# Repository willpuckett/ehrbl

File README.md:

# 🍁 ehrbl

> a tiny board to celebrate the coming of 🍂 with minimal finger travel.

After spending the day at my computer, I stepped out with friends Saturday night
for a burger. On the patio of our local institution, the air was
cool.

> _Autumn had undeniably arrived._

I had been wanting to squeeze a Ferris Sweep out of a Xiao somehow and it
occurred to me as I later continued working that maybe I was actually trying to
make a 28 key keyboard. I reached for a leaf to lay over the keys: the maple fit
nicely, conjuring memories of _beurre d'érable_ (maple butter) in Montreal's
Jean-Talon Market.

## BOM

|      QTY      |             Part             | JLCPCB Part # |
| :-----------: | :--------------------------: | :-----------: |
|       2       |         MY-LR44-03-J         |   C5457116    |
|       4       |       100 nF 0402 cap        |    C60474     |
|       2       |          SSSS811101          |    C109335    |
|       4       |      MF254V-11-07-0743       |   C2889988    |
|       6       |          CESD5V0D3           |    C22643     |
|       2       |   0906-2-15-20-75-14-11-0    |   C5261048    |
|       8       |           UMP1NTR            |    C510065    |
| 56 (optional) |   3305-0-15-80-47-27-10-0    |   C17370797   |
|     26/28     |       ChocV1 switches        |      N/A      |
| 2 (optional)  | Panasonic EVQWGD001 encoders |      N/A      |
|       2       |   3.7V LIR1254 (NOT LR44)    |      N/A      |
|       2       |        Xiao nRF52840         |      N/A      |

## Putting it Together

### Fabrication & Assembly Files [[zip](https://github.com/willpuckett/ehrbl/releases/latest/download/jlcpcb.zip)]

JLC likes to install the 3305's upside down. Include
[this pic](.images/3305-installation.png) along with a note requesting they be
installed thru-hole.

Choose 28 keys, or 26 keys with encoders.

> [!CAUTION]
> Use **3.7v LIR1254** (lithium ion rechargable) battery **only**, being sure to
> not install it upside down.

Also available [here](https://octule.com/listing/1842166746/ehrbl).

## Case

### There's a case [[step](https://github.com/willpuckett/ehrbl/releases/latest/download/case.step)] [[stl](https://github.com/willpuckett/ehrbl/releases/latest/download/case.step)]

It's really more of a skin. It is designed to sit as low as possible.Print and place the pcb directly in it. The case is
only one half, flip it in your slicer for the other half 🙃

> [!TIP]
> Polymaker TPU works well. It seems to like to print slow and cool—leave the
> door ajar.

TPU is relatively non-slip, and it absorbs and distributes the force of
typing—no bumpons necessary.

## Caster

### Download the latest firmware [[left](https://github.com/willpuckett/ehrbl/releases/latest/download/ehrbl-central.uf2)] [[right](https://github.com/willpuckett/ehrbl/releases/latest/download/ehrbl-peripheral.uf2)]

Using a variant that should probably be referred to as _Befuddle_, scoring a
whispy 636.1 "total word effort" on
[cyanophage](https://cyanophage.github.io/playground.html?layout=bfdl%2F%3Bpouyjcstrx-naihqvwgm%5C%3Dk%2C.%27ze&mode=ergo&lan=english), this maple is buttery indeed. The Y-punctuation cluster interaction is its greatest shortcoming, but it seems
to be the least of all evils and becomes more natural after a week or so.

Optimized for single handed CAD—Blender, KiCad, Shapr... Hold num/caps word to access the upside down sticky layer which reverses the keys. You'll have all the alphas on both hands and don't have to switch back and forth from mouse/trackpad so much.

> [!NOTE]
> The combo-forward layout obscures CAGS home row mods in the graphics.

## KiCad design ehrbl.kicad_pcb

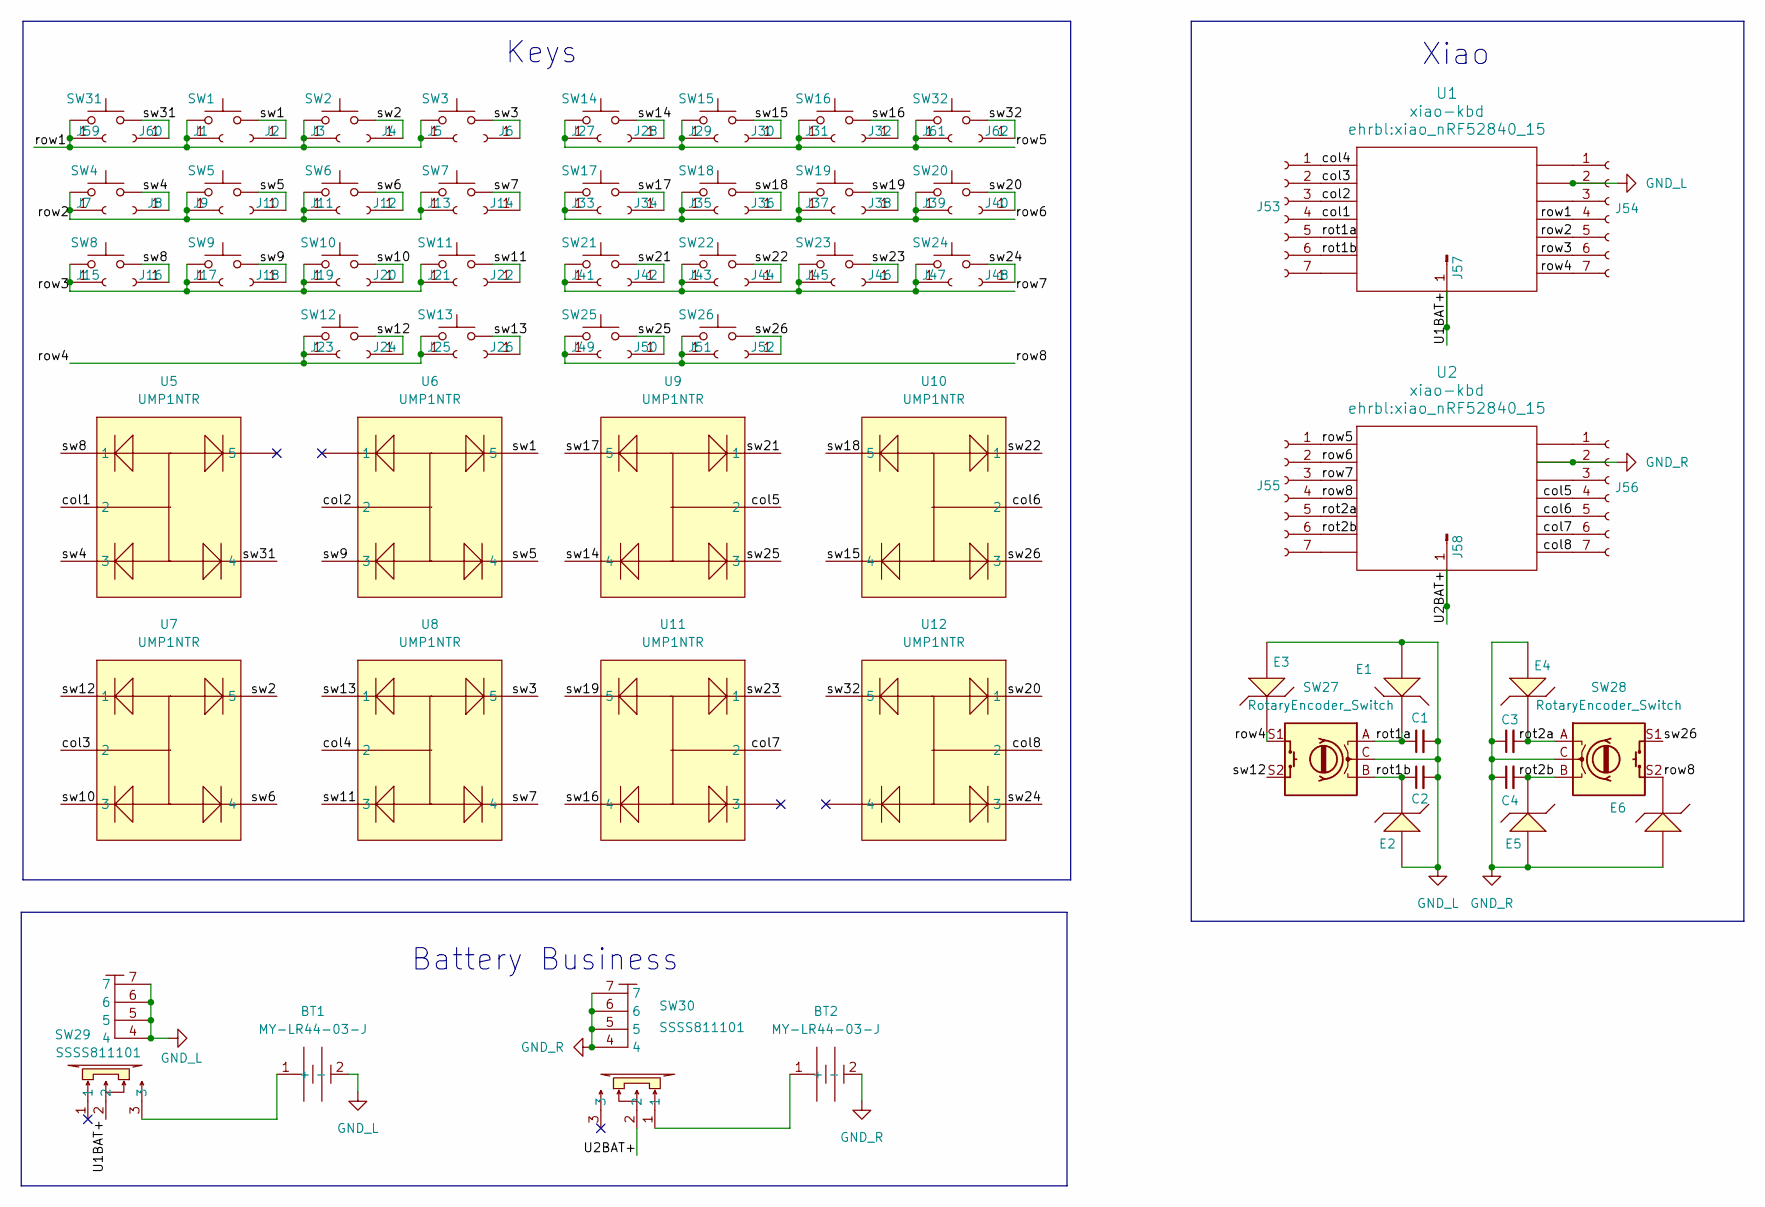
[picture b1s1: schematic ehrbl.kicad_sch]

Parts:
BT1, BT2: MY-LR44-03-J; CONN-TH_MY-LR44-03-J; LCSC C5457116
C1, C2, C3, C4: C_Small; C_0402_1005Metric; LCSC C60474
E1, E2, E3, E4, E5, E6: CESD5V0D3 ZA; SOD-323_L1.8-W1.3-LS2.5-RD; LCSC C22643
J1, J2, J3, J4, J5, J6, J7, J8, J9, J10, J11, J12, J13, J14, J15, J16, J17, J18, J19, J20, J21, J22, J23, J24, J25, J26, J27, J28, J29, J30, J31, J32, J33, J34, J35, J36, J37, J38, J39, J40, J41, J42, J43, J44, J45, J46, J47, J48, J49, J50, J51, J52, J59, J60, J61, J62: 3305-0-15-80-47-27-10-0; MPN 3305-0-15-80-47-27-10-0; LCSC C17370797
J53, J54, J55, J56: MF254V-11-07-0743; MPN 310-13-107-41-001000; LCSC C2889988
J57, J58: 0906; 0906-2-15-20-75-14-11-0; MPN 0906-2-15-20-75-14-11-0; LCSC C5261048
SW1, SW2, SW3, SW4, SW5, SW6, SW7, SW8, SW9, SW10, SW11, SW12, SW13, SW14, SW15, SW16, SW17, SW18, SW19, SW20, SW21, SW22, SW23, SW24, SW25, SW26, SW31, SW32: SW_Push; SW_PG1350
SW27, SW28: RotaryEncoder_Switch; RollerEncoder_Panasonic_EVQWGD001
SW29, SW30: SSSS811101; SW-SMD_SSSS811101; LCSC C109335
U1, U2: xiao-kbd; xiao_nRF52840_15
U5, U7, U8, U9, U10, U11, U12: UMP1NTR; SOT-353_L2.1-W1.3-P0.65-LS2.3-BL; LCSC Part C510065
U6: UMP1NTR; SOT-353_L2.1-W1.3-P0.65-LS2.3-BL; LCSC C510065

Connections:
/U1BAT+: J57.1, SW29.2, U1.15 (BAT+)
/U2BAT+: J58.1, SW30.2, U2.15 (BAT+)
/col1: J53.4, U1.4 (D3), U5.2
/col2: J53.3, U1.3 (D2), U6.2
/col3: J53.2, U1.2 (D1), U7.2
/col4: J53.1, U1.1 (D0), U8.2
/col5: J56.4, U2.11 (D10), U9.2
/col6: J56.5, U2.10 (D9), U10.2
/col7: J56.6, U2.9 (D8), U11.2
/col8: J56.7, U2.8 (D7), U12.2
/rot1a: C1.1, E1.1, J53.5, SW27.A, U1.5 (D4)
/rot1b: C2.1, E2.1, J53.6, SW27.B, U1.6 (D5)
/rot2a: C3.2, E4.1, J55.5, SW28.A, U2.5 (D4)
/rot2b: C4.2, E5.1, J55.6, SW28.B, U2.6 (D5)
/row1: J1.1, J3.1, J5.1, J54.4, J59.1, SW1.1, SW2.1, SW3.1, SW31.1, U1.11 (D10)
/row2: J7.1, J9.1, J11.1, J13.1, J54.5, SW4.1, SW5.1, SW6.1, SW7.1, U1.10 (D9)
/row3: J15.1, J17.1, J19.1, J21.1, J54.6, SW8.1, SW9.1, SW10.1, SW11.1, U1.9 (D8)
/row4: E3.1, J23.1, J25.1, J54.7, SW12.1, SW13.1, SW27.S1, U1.8 (D7)
/row5: J27.1, J29.1, J31.1, J55.1, J61.1, SW14.1, SW15.1, SW16.1, SW32.1, U2.1 (D0)
/row6: J33.1, J35.1, J37.1, J39.1, J55.2, SW17.1, SW18.1, SW19.1, SW20.1, U2.2 (D1)
/row7: J41.1, J43.1, J45.1, J47.1, J55.3, SW21.1, SW22.1, SW23.1, SW24.1, U2.3 (D2)
/row8: E6.1, J49.1, J51.1, J55.4, SW25.1, SW26.1, SW28.S2, U2.4 (D3)
/sw1: J2.1, SW1.2, U6.5
/sw2: J4.1, SW2.2, U7.5
/sw3: J6.1, SW3.2, U8.5
/sw4: J8.1, SW4.2, U5.3
/sw5: J10.1, SW5.2, U6.4
/sw6: J12.1, SW6.2, U7.4
/sw7: J14.1, SW7.2, U8.4
/sw8: J16.1, SW8.2, U5.1
/sw9: J18.1, SW9.2, U6.3
/sw10: J20.1, SW10.2, U7.3
/sw11: J22.1, SW11.2, U8.3
/sw12: J24.1, SW12.2, SW27.S2, U7.1
/sw13: J26.1, SW13.2, U8.1
/sw14: J28.1, SW14.2, U9.4
/sw15: J30.1, SW15.2, U10.4
/sw16: J32.1, SW16.2, U11.4
/sw17: J34.1, SW17.2, U9.5
/sw18: J36.1, SW18.2, U10.5
/sw19: J38.1, SW19.2, U11.5
/sw20: J40.1, SW20.2, U12.1
/sw21: J42.1, SW21.2, U9.1
/sw22: J44.1, SW22.2, U10.1
/sw23: J46.1, SW23.2, U11.1
/sw24: J48.1, SW24.2, U12.3
/sw25: J50.1, SW25.2, U9.3
/sw26: J52.1, SW26.2, SW28.S1, U10.3
/sw31: J60.1, SW31.2, U5.4
/sw32: J62.1, SW32.2, U12.5
GND_L: BT1.2 (-), C1.2, C2.2, E1.2, E2.2, E3.2, J54.2, SW27.C, SW29.4, SW29.5, SW29.6, SW29.7, U1.13 (GND)
GND_R: BT2.2 (-), C3.1, C4.1, E4.2, E5.2, E6.2, J56.2, SW28.C, SW30.4, SW30.5, SW30.6, SW30.7, U2.13 (GND)
unnamed: BT1.1 (+), SW29.3
unnamed: BT2.1 (+), SW30.1
unnamed: J53.7, U1.7 (D6)
unnamed: J54.1, U1.14 (5v)
unnamed: J54.3, U1.12 (3v3)
unnamed: J55.7, U2.7 (D6)
unnamed: J56.1, U2.14 (5v)
unnamed: J56.3, U2.12 (3v3)

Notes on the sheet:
Battery Business
Keys
Xiao

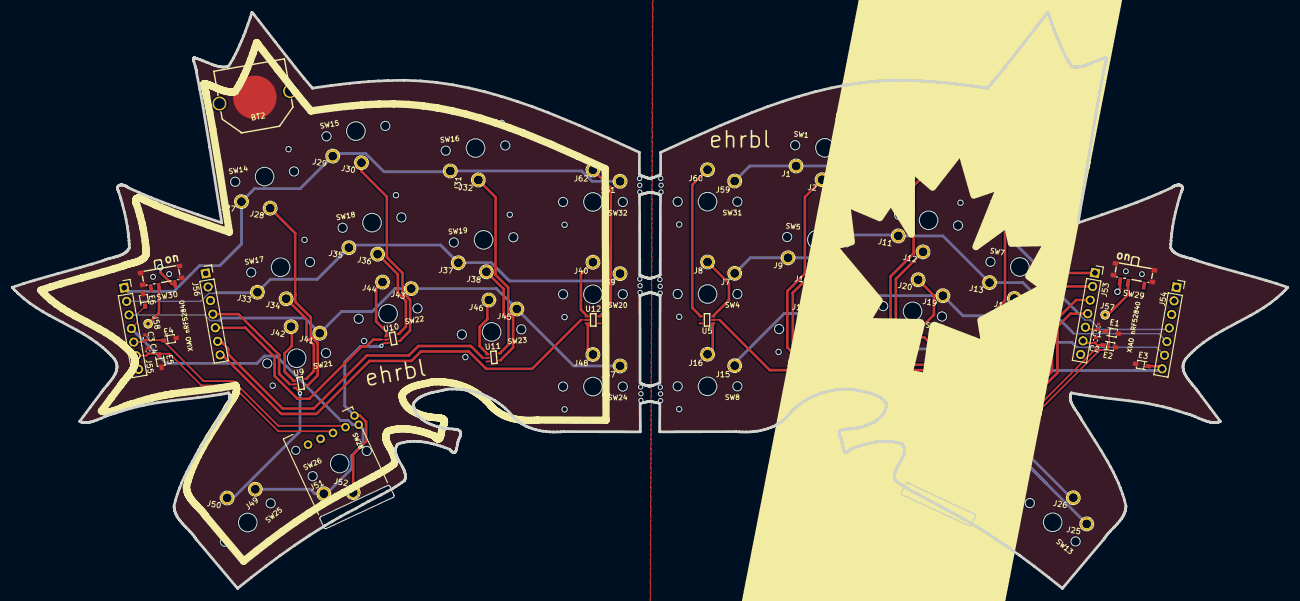
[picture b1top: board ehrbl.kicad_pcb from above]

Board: 2 copper layers, 234.9 x 106.1 mm, 116 parts (0 on the bottom side), 60 nets.

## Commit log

2024-11-15 shorten b/v combo timing, add pristine option to local build script
2024-11-15 attempting to improve shift
2024-11-15 add pkgx for build123d installation
2024-11-16 add magics, and pristine flag for local builds...
2024-11-16 rework nordrassil bottom left row
2024-11-19 switch to caster
2024-11-21 smooth out caster
2024-11-26 back to 28 keys
2024-11-26 fix build.yml names
2024-11-26 fix readme typo
2024-11-28 improve keymap readability
2024-11-28 clean up silkscreen
2024-11-28 add dongle
2024-11-28 move case line of symmetry
2024-12-27 clean up dongle, add rmk
2025-01-04 update rmk to 0.5.1; switch to cargo-hex
2025-01-04 add upside down layer
2025-01-04 add upside down to right hand
2025-01-05 add kp keys to num_word continue list
2025-01-09 change combo timing
2025-01-09 switch keycaps to klp-lame
2025-01-09 update render
2025-01-09 fix drc violations
2025-01-13 add link, render files
2025-01-16 refine upside down layer & combos
2025-01-28 update rmk
2025-01-28 improve USD
2025-02-27 add 3305 images
2025-02-27 VGMW
2025-03-11 combos in RMK
2025-10-31 archive zmk to separate branch
2025-10-31 move zmk to separate branch
2025-10-31 update actions
2025-10-31 clean up
2025-10-31 add .DS_Store to .gitignore
2025-10-31 remove ehrbl-layouts.dtsi workflow file
2025-10-31 update README.md for case description and firmware download links
2025-10-31 bump version of rmk-nrf52840 to 0.2.1
2025-10-31 bump version to 0.2.2
